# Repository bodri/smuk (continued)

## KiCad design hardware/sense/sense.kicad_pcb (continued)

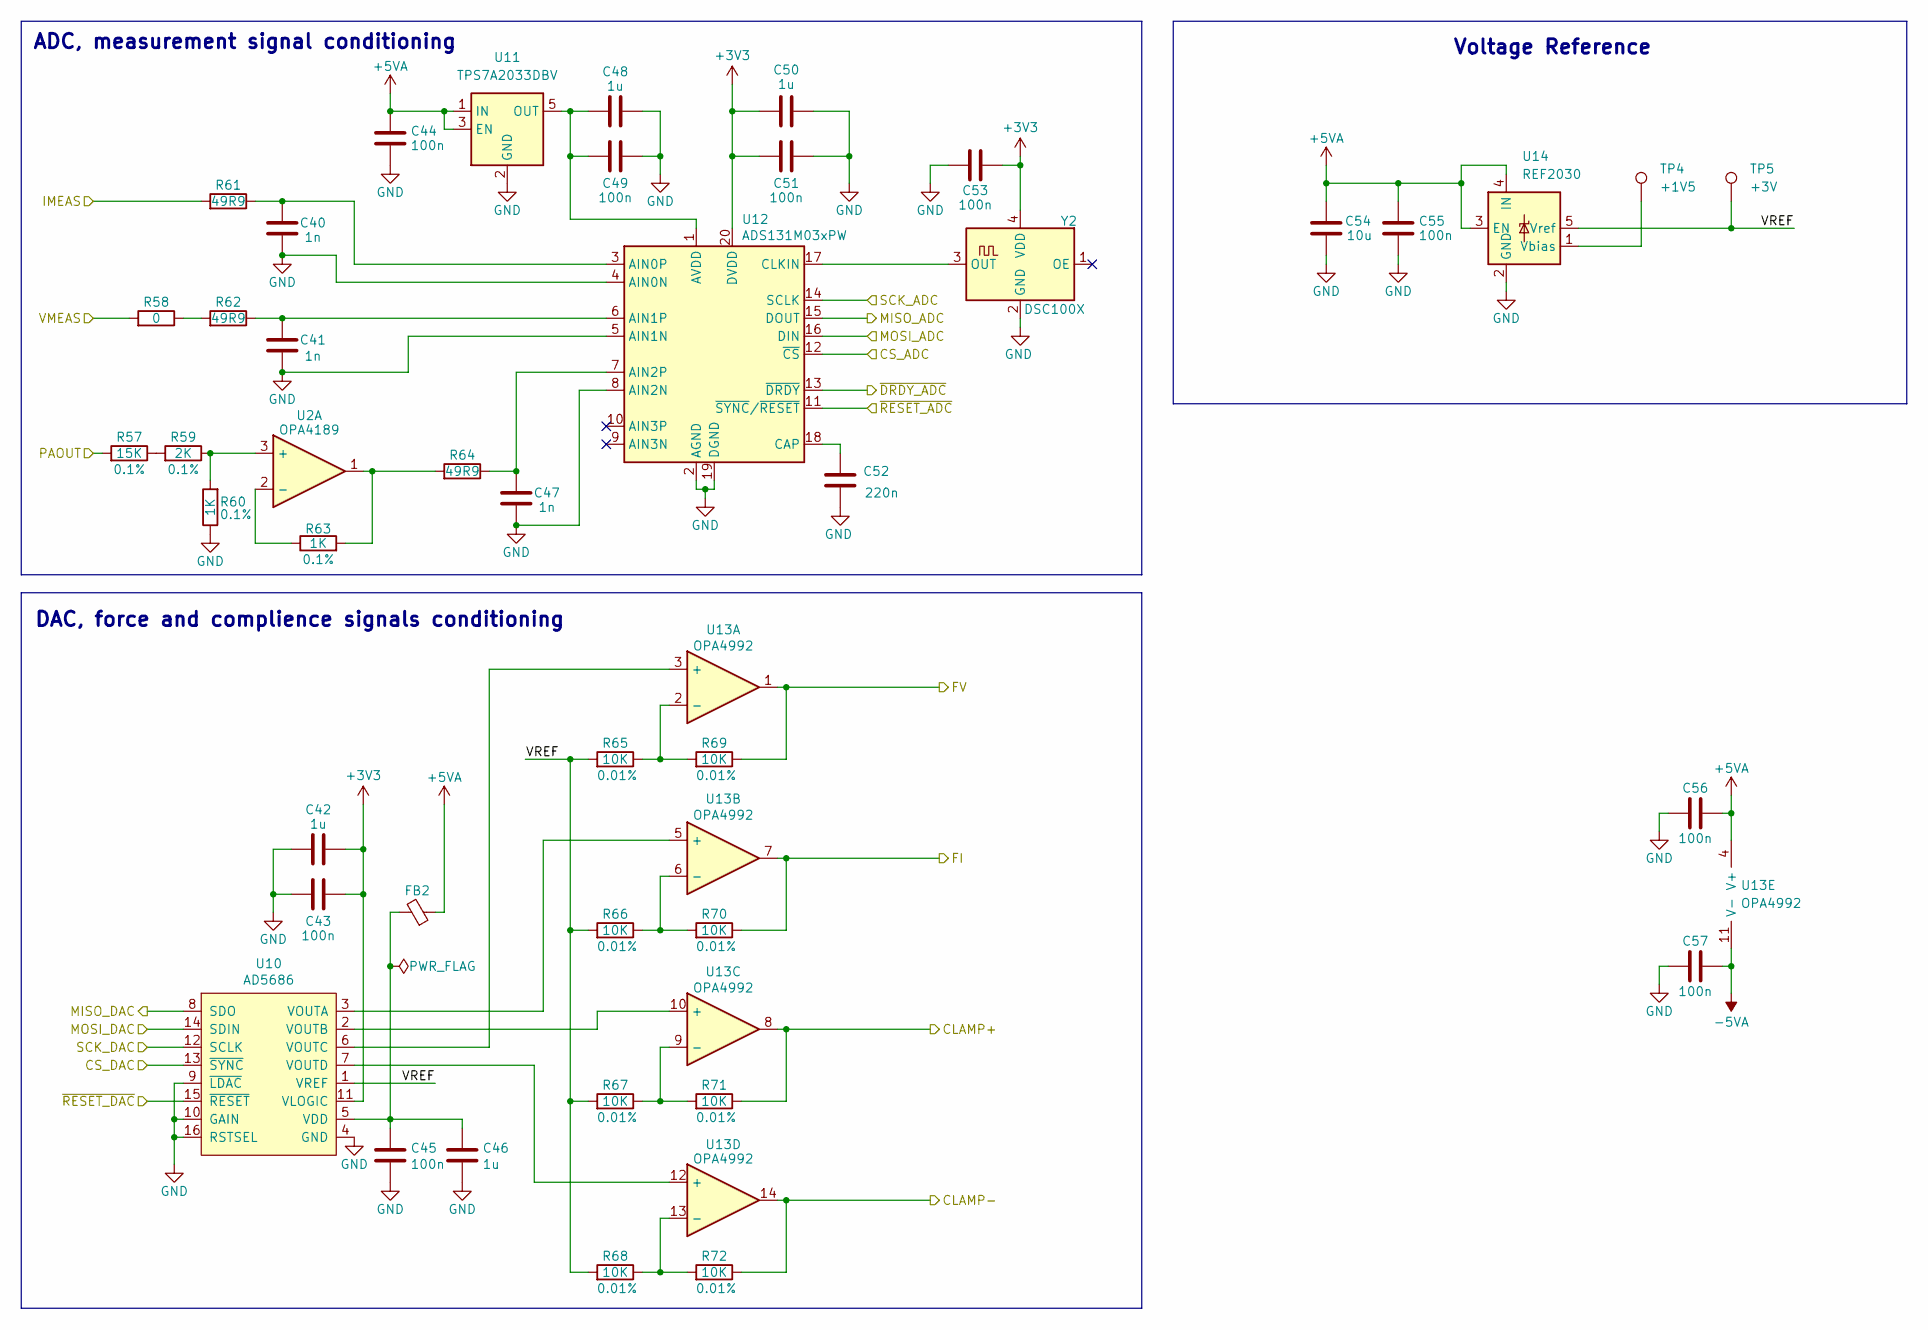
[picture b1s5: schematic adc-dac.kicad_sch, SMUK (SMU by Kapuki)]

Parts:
C40, C41, C47: 1n; C_0603_1608Metric
C42, C46, C48, C50: 1u; C_0603_1608Metric
C43, C44, C45, C49, C51, C53, C55, C56, C57: 100n; C_0603_1608Metric
C52: 220n; C_0603_1608Metric
C54: 10u; C_0603_1608Metric
FB2: FerriteBead_Small; L_0603_1608Metric
R57: 15K; R_0603_1608Metric
R58: 0; R_1206_3216Metric
R59: 2K; R_0603_1608Metric
R60, R63: 1K; R_0603_1608Metric
R61, R62, R64: 49R9; R_0603_1608Metric
R65, R66, R67, R68, R69, R70, R71, R72: 10K; R_0603_1608Metric
TP4: +1V5; TestPoint_Pad_D1.5mm
TP5: +3V; TestPoint_Pad_D1.5mm
U2: OPA4189; TSSOP-14_4.4x5mm_P0.65mm
U10: AD5686; TSSOP-16_4.4x5mm_P0.65mm
U11: TPS7A2033DBV; SOT-23-5
U12: ADS131M03xPW; TSSOP-20_4.4x6.5mm_P0.65mm
U13: OPA4992; TSSOP-14_4.4x5mm_P0.65mm
U14: REF2030; SOT-23-5
Y2: DSC100X; CDFN-4_2.5x3.2mm_P2.1mm

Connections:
+3V3: C42.2, C43.2, C50.2, C51.2, C53.2, U10.11 (VLOGIC), U12.20 (DVDD), Y2.4 (VDD); also elsewhere on the board
+5VA: C44.1, C54.1, C55.1, C56.1, FB2.1, U11.1 (IN), U11.3 (EN), U13.4 (V+), U14.3 (EN), U14.4 (IN); also elsewhere on the board
-5VA: C57.1, U13.11 (V-); also elsewhere on the board
/ADC & DAC/CLAMP+: R71.1, U13.8; also elsewhere on the board
/ADC & DAC/CLAMP-: R72.1, U13.14; also elsewhere on the board
/ADC & DAC/CS_ADC: U12.12 (~CS); also elsewhere on the board
/ADC & DAC/CS_DAC: U10.13 (~SYNC); also elsewhere on the board
/ADC & DAC/FI: R70.1, U13.7; also elsewhere on the board
/ADC & DAC/FV: R69.1, U13.1; also elsewhere on the board
/ADC & DAC/IMEAS: R61.2; also elsewhere on the board
/ADC & DAC/MISO_ADC: U12.15 (DOUT); also elsewhere on the board
/ADC & DAC/MISO_DAC: U10.8 (SDO); also elsewhere on the board
/ADC & DAC/MOSI_ADC: U12.16 (DIN); also elsewhere on the board
/ADC & DAC/MOSI_DAC: U10.14 (SDIN); also elsewhere on the board
/ADC & DAC/PAOUT: R57.2; also elsewhere on the board
/ADC & DAC/SCK_ADC: U12.14 (SCLK); also elsewhere on the board
/ADC & DAC/SCK_DAC: U10.12 (SCLK); also elsewhere on the board
/ADC & DAC/VMEAS: R58.2; also elsewhere on the board
/ADC & DAC/VREF: R65.2, R66.2, R67.2, R68.2, TP5.1 (1_1), U10.1 (VREF), U14.5 (Vref)
/ADC & DAC/~DRDY_ADC: U12.13 (~DRDY); also elsewhere on the board
/ADC & DAC/~RESET_ADC: U12.11 (~SYNC/~RESET); also elsewhere on the board
/ADC & DAC/~RESET_DAC: U10.15 (~RESET); also elsewhere on the board
GND: C40.2, C41.2, C42.1, C43.1, C44.2, C45.2, C46.2, C47.2, C48.1, C49.1, C50.1, C51.1, C52.2, C53.1, C54.2, C55.2, C56.2, C57.2, R60.1, U10.4 (GND), U10.9 (~LDAC), U10.10 (GAIN), U10.16 (RSTSEL), U11.2 (GND), U12.2 (AGND), U12.4 (AIN0N), U12.5 (AIN1N), U12.8 (AIN2N), U12.19 (DGND), U14.2 (GND), Y2.2 (GND); also elsewhere on the board
unnamed: R57.1, R59.2
unnamed: R58.1, R62.2
unnamed: R63.2, R64.2, U2.1
unnamed: R59.1, R60.2, U2.3 (+)
unnamed: R63.1, U2.2 (-)
unnamed: C45.1, C46.1, FB2.2, U10.5 (VDD)
unnamed: U10.3 (VOUTA), U13.5 (+)
unnamed: U10.2 (VOUTB), U13.10 (+)
unnamed: U10.6 (VOUTC), U13.3 (+)
unnamed: U10.7 (VOUTD), U13.12 (+)
unnamed: C48.2, C49.2, U11.5 (OUT), U12.1 (AVDD)
unnamed: C40.1, R61.1, U12.3 (AIN0P)
unnamed: C41.1, R62.1, U12.6 (AIN1P)
unnamed: C47.1, R64.1, U12.7 (AIN2P)
unnamed: C52.1, U12.18 (CAP)
unnamed: U12.17 (CLKIN), Y2.3 (OUT)
unnamed: R65.1, R69.2, U13.2 (-)
unnamed: R66.1, R70.2, U13.6 (-)
unnamed: R67.1, R71.2, U13.9 (-)
unnamed: R68.1, R72.2, U13.13 (-)
unnamed: TP4.1 (1_1), U14.1 (Vbias)

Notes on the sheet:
ADC, measurement signal conditioning
DAC, force and complience signals conditioning
Voltage Reference

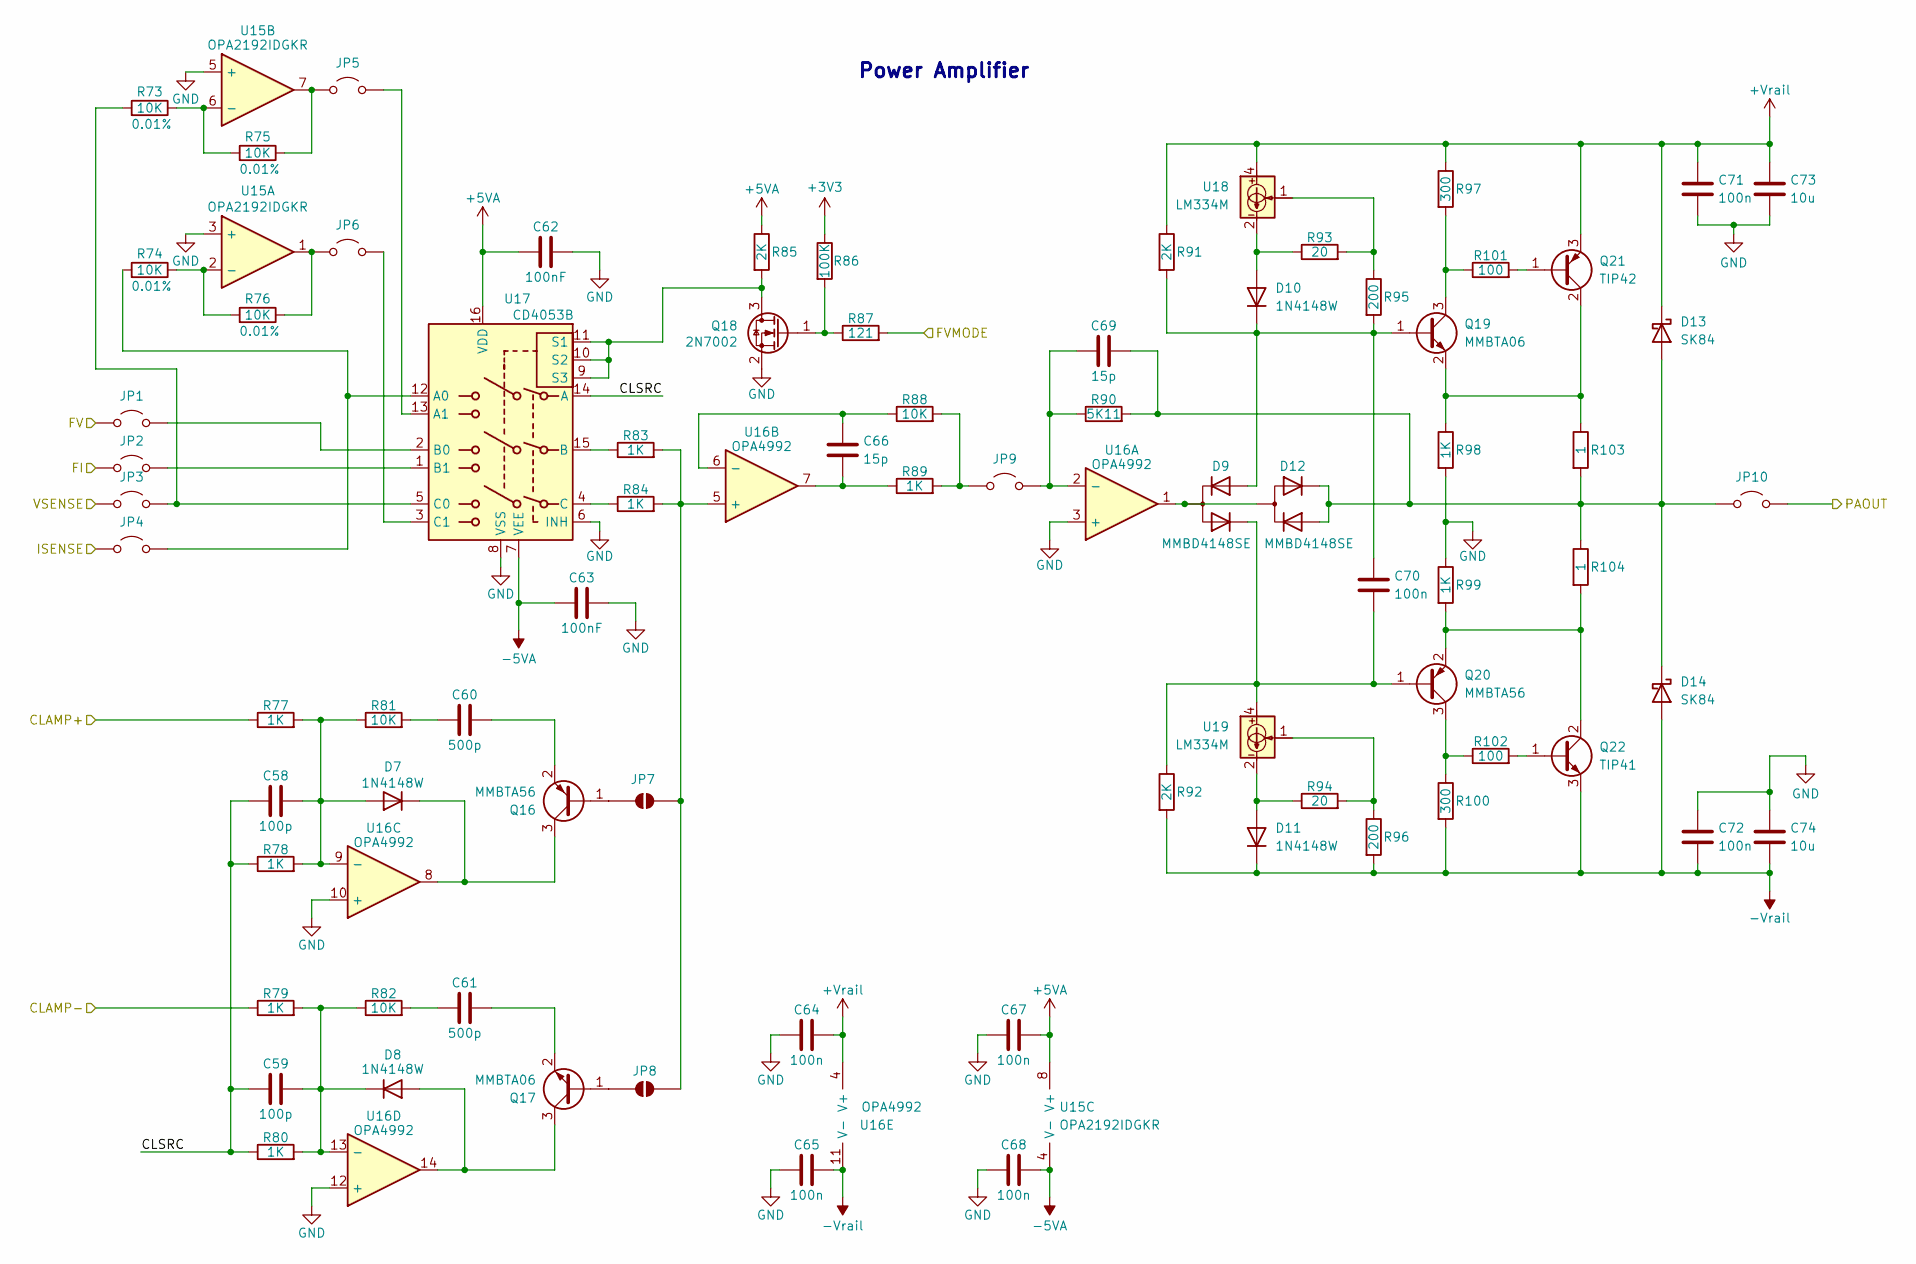
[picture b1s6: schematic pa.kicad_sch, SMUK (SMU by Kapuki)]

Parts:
C58, C59: 100p; C_0603_1608Metric
C60, C61: 500p; C_0603_1608Metric
C62, C63: 100nF; C_0603_1608Metric
C64, C65, C67, C68: 100n; C_0603_1608Metric
C66: 15p; C_0603_1608Metric
C69: 15p; C_1206_3216Metric
C70, C71, C72: 100n; C_1206_3216Metric
C73, C74: 10u; C_1210_3225Metric
D7, D8, D10, D11: 1N4148W; D_SOD-123
D9, D12: MMBD4148SE; SOT-23
D13, D14: SK84; D_SMC
JP1, JP2, JP3, JP4, JP5, JP6, JP9, JP10: Jumper_2_Open; TestPoint_2Pads_Pitch2.54mm_Drill0.8mm
JP7, JP8: SolderJumper_2_Open; SolderJumper-2_P1.3mm_Open_RoundedPad1.0x1.5mm
Q16, Q20: MMBTA56; SOT-23
Q17, Q19: MMBTA06; SOT-23
Q18: 2N7002; SOT-23
Q21: TIP42; TO-220-3_Vertical
Q22: TIP41; TO-220-3_Vertical
R73, R74, R75, R76, R81, R82, R88: 10K; R_0603_1608Metric
R77, R78, R79, R80, R89: 1K; R_0603_1608Metric
R83, R84: 1K; R_1206_3216Metric
R85: 2K; R_0603_1608Metric
R86: 100K; R_0603_1608Metric
R87: 121; R_0603_1608Metric
R90: 5K11; R_1206_3216Metric
R91, R92: 2K; R_1206_3216Metric
R93, R94: 20; R_0805_2012Metric
R95, R96: 200; R_0805_2012Metric
R97, R100: 300; R_0805_2012Metric
R98, R99: 1K; R_2512_6332Metric
R101, R102: 100; R_0805_2012Metric
R103, R104: 1; R_2512_6332Metric
U15: OPA2192IDGKR; VSSOP-8_3x3mm_P0.65mm
U16: OPA4992; TSSOP-14_4.4x5mm_P0.65mm
U17: CD4053B; TSSOP-16_4.4x5mm_P0.65mm
U18, U19: LM334M; SOIC-8_3.9x4.9mm_P1.27mm

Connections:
+3V3: R86.1; also elsewhere on the board
+5VA: C62.1, C67.1, R85.1, U15.8 (V+), U17.16 (VDD); also elsewhere on the board
+Vrail: C64.1, C71.1, C73.1, D13.1 (K), Q21.3 (E), R91.1, R97.1, U16.4 (V+), U18.4; also elsewhere on the board
-5VA: C63.1, C68.1, U15.4 (V-), U17.7 (VEE); also elsewhere on the board
-Vrail: C65.1, C72.2, C74.2, D11.1 (K), D14.2 (A), Q22.3 (E), R92.2, R96.2, R100.2, U16.11 (V-); also elsewhere on the board
/ADC & DAC/CLAMP+: R77.1; also elsewhere on the board
/ADC & DAC/CLAMP-: R79.1; also elsewhere on the board
/ADC & DAC/FI: JP2.1 (A); also elsewhere on the board
/ADC & DAC/FV: JP1.1 (A); also elsewhere on the board
/ADC & DAC/PAOUT: JP10.2 (B); also elsewhere on the board
/Current Sense/ISENSE: JP4.1 (A); also elsewhere on the board
/Floating MCU/FVMODE: R87.2; also elsewhere on the board
/Power Amplifier/CLSRC: C58.1, C59.1, R78.1, R80.1, U17.14 (A)
/Power Amplifier/VSENSE: JP3.1 (A); also elsewhere on the board
GND: C62.2, C63.2, C64.2, C65.2, C67.2, C68.2, C71.2, C72.1, C73.2, C74.1, Q18.2 (S), R98.2, R99.1, U15.3 (+), U15.5 (+), U16.3 (+), U16.10 (+), U16.12 (+), U17.6 (INH), U17.8 (VSS); also elsewhere on the board
unnamed: C60.1, R81.2
unnamed: C61.1, R82.2
unnamed: C66.2, R89.1, U16.7
unnamed: C58.2, D7.2 (A), R77.2, R78.2, R81.1, U16.9 (-)
unnamed: D7.1 (K), Q16.3 (C), U16.8
unnamed: D8.2 (A), Q17.3 (C), U16.14
unnamed: C59.2, D8.1 (K), R79.2, R80.2, R82.1, U16.13 (-)
unnamed: D10.2 (A), R93.1, U18.2, U18.3, U18.6, U18.7
unnamed: C70.1, D9.1, D10.1 (K), Q19.1 (B), R91.2, R95.2
unnamed: D11.2 (A), R94.1, U19.2, U19.3, U19.6, U19.7
unnamed: D9.3, D12.3, U16.1
unnamed: C69.2, D12.1, D12.2, D13.2 (A), D14.1 (K), JP10.1 (A), R90.2, R103.2, R104.1
unnamed: JP1.2 (B), U17.2 (B0)
unnamed: JP2.2 (B), U17.1 (B1)
unnamed: JP3.2 (B), R73.2, U17.5 (C0)
unnamed: JP4.2 (B), R74.2, U17.12 (A0)
unnamed: JP5.1 (A), R75.1, U15.7
unnamed: JP5.2 (B), U17.13 (A1)
unnamed: JP6.1 (A), R76.1, U15.1
unnamed: JP6.2 (B), U17.3 (C1)
unnamed: JP7.1 (A), Q16.1 (B)
unnamed: JP7.2 (B), JP8.2 (B), R83.2, R84.2, U16.5 (+)
unnamed: JP8.1 (A), Q17.1 (B)
unnamed: JP9.1 (A), R88.2, R89.2
unnamed: C69.1, JP9.2 (B), R90.1, U16.2 (-)
unnamed: C60.2, Q16.2 (E)
unnamed: C61.2, Q17.2 (E)
unnamed: Q18.3 (D), R85.2, U17.9 (S3), U17.10 (S2), U17.11 (S1)
unnamed: Q18.1 (G), R86.2, R87.1
unnamed: Q19.3 (C), R97.2, R101.1
unnamed: Q19.2 (E), Q21.2 (C), R98.1, R103.1
unnamed: C70.2, D9.2, Q20.1 (B), R92.1, U19.4
unnamed: Q20.3 (C), R100.1, R102.1
unnamed: Q20.2 (E), Q22.2 (C), R99.2, R104.2
unnamed: Q21.1 (B), R101.2
unnamed: Q22.1 (B), R102.2
unnamed: R93.2, R95.1, U18.1
unnamed: R94.2, R96.1, U19.1
unnamed: R74.1, R76.2, U15.2 (-)
unnamed: R73.1, R75.2, U15.6 (-)
unnamed: C66.1, R88.1, U16.6 (-)
unnamed: R83.1, U17.15 (B)
unnamed: R84.1, U17.4 (C)

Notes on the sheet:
Power Amplifier

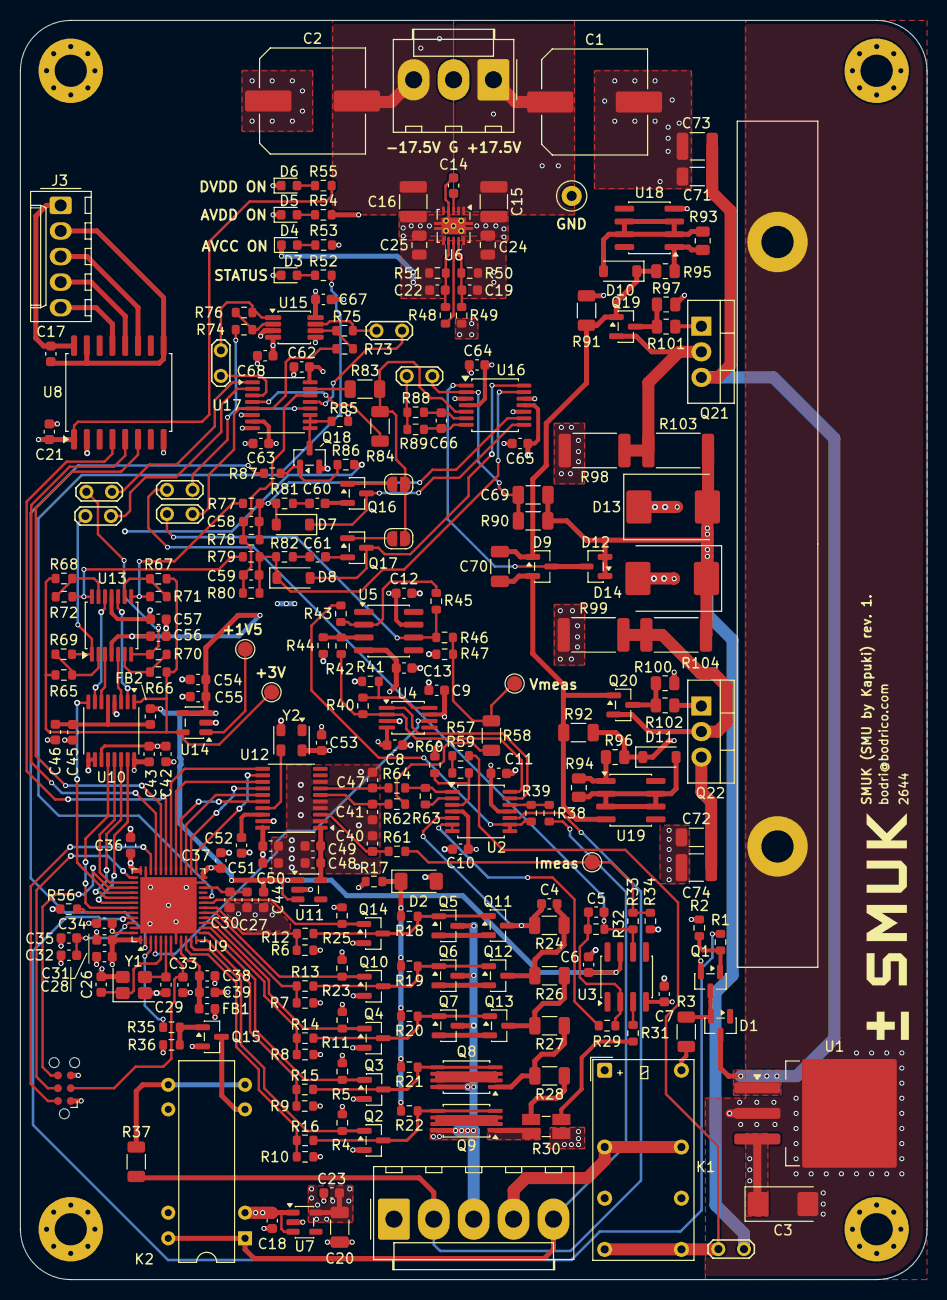
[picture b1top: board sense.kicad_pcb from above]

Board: 4 copper layers, 90.0 x 125.0 mm, 263 parts (0 on the bottom side), 172 nets.

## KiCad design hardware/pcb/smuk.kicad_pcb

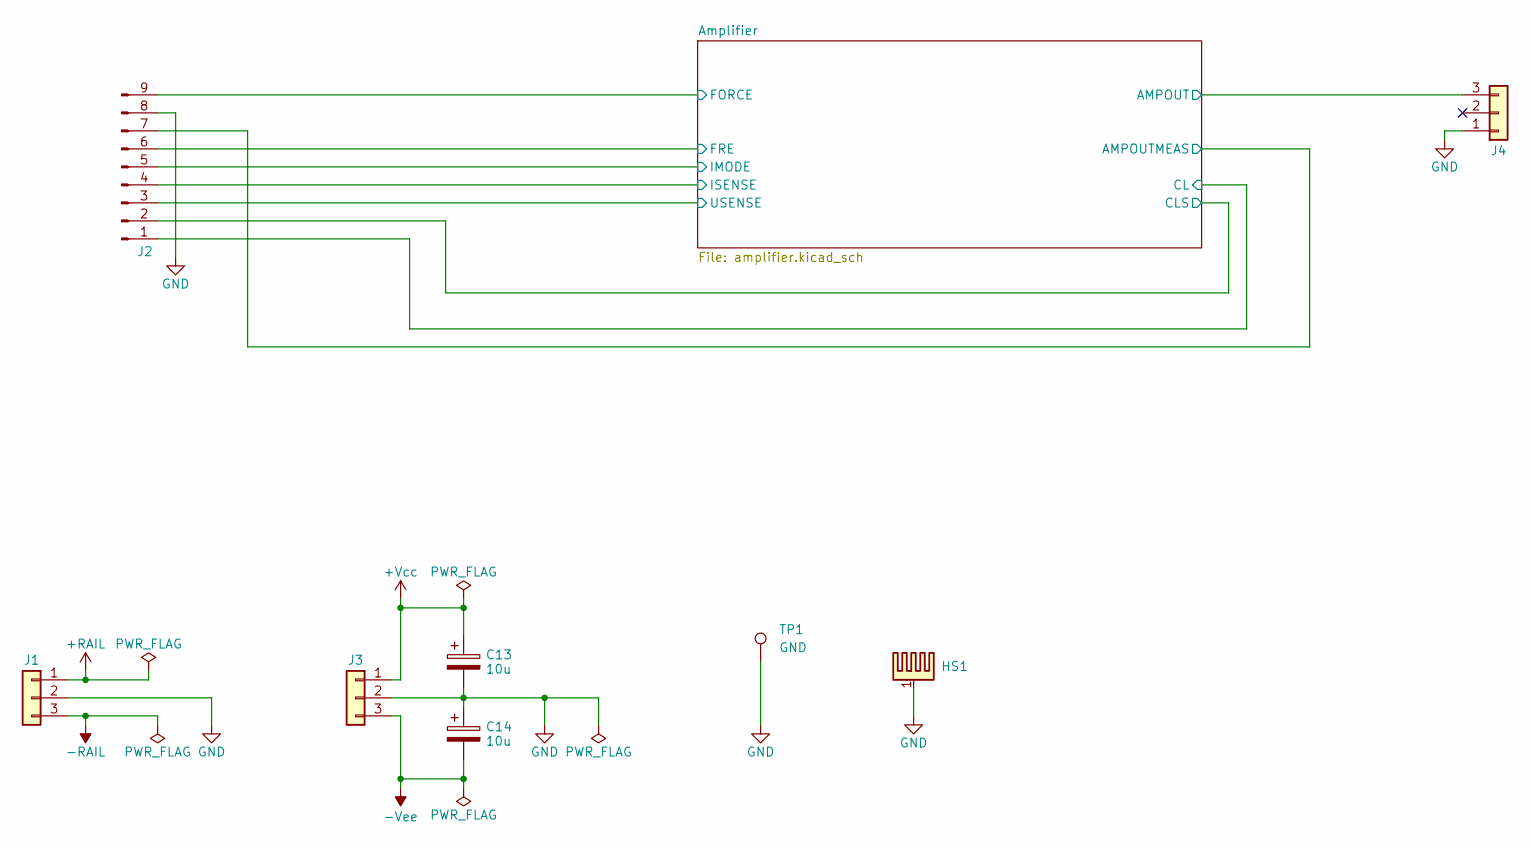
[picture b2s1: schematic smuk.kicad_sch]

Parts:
C13, C14: 10u; CP_EIA-6032-28_Kemet-C
HS1: Heatsink_Pad; Heatsink_Fischer_SK96-84SA_2Fixations
J1, J3, J4: Conn_01x03; Molex_KK-396_A-41791-0003_1x03_P3.96mm_Vertical
J2: Conn_01x09_Pin; PinHeader_1x09_P2.54mm_Horizontal
TP1: GND; TestPoint_Loop_D1.80mm_Drill1.0mm_Beaded

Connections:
+RAIL: J1.1; also elsewhere on the board
+Vcc: C13.1, J3.1; also elsewhere on the board
-RAIL: J1.3; also elsewhere on the board
-Vee: C14.2, J3.3; also elsewhere on the board
/Amplifier/AMPOUT: J4.3; also elsewhere on the board
/Amplifier/AMPOUTMEAS: J2.7; also elsewhere on the board
/Amplifier/CL: J2.1; also elsewhere on the board
/Amplifier/CLS: J2.2; also elsewhere on the board
/Amplifier/FORCE: J2.9; also elsewhere on the board
/Amplifier/FRE: J2.6; also elsewhere on the board
/Amplifier/IMODE: J2.5; also elsewhere on the board
/Amplifier/ISENSE: J2.4; also elsewhere on the board
/Amplifier/USENSE: J2.3; also elsewhere on the board
GND: C13.2, C14.1, HS1.1, J1.2, J2.8, J3.2, J4.1, TP1.1 (1_1); also elsewhere on the board

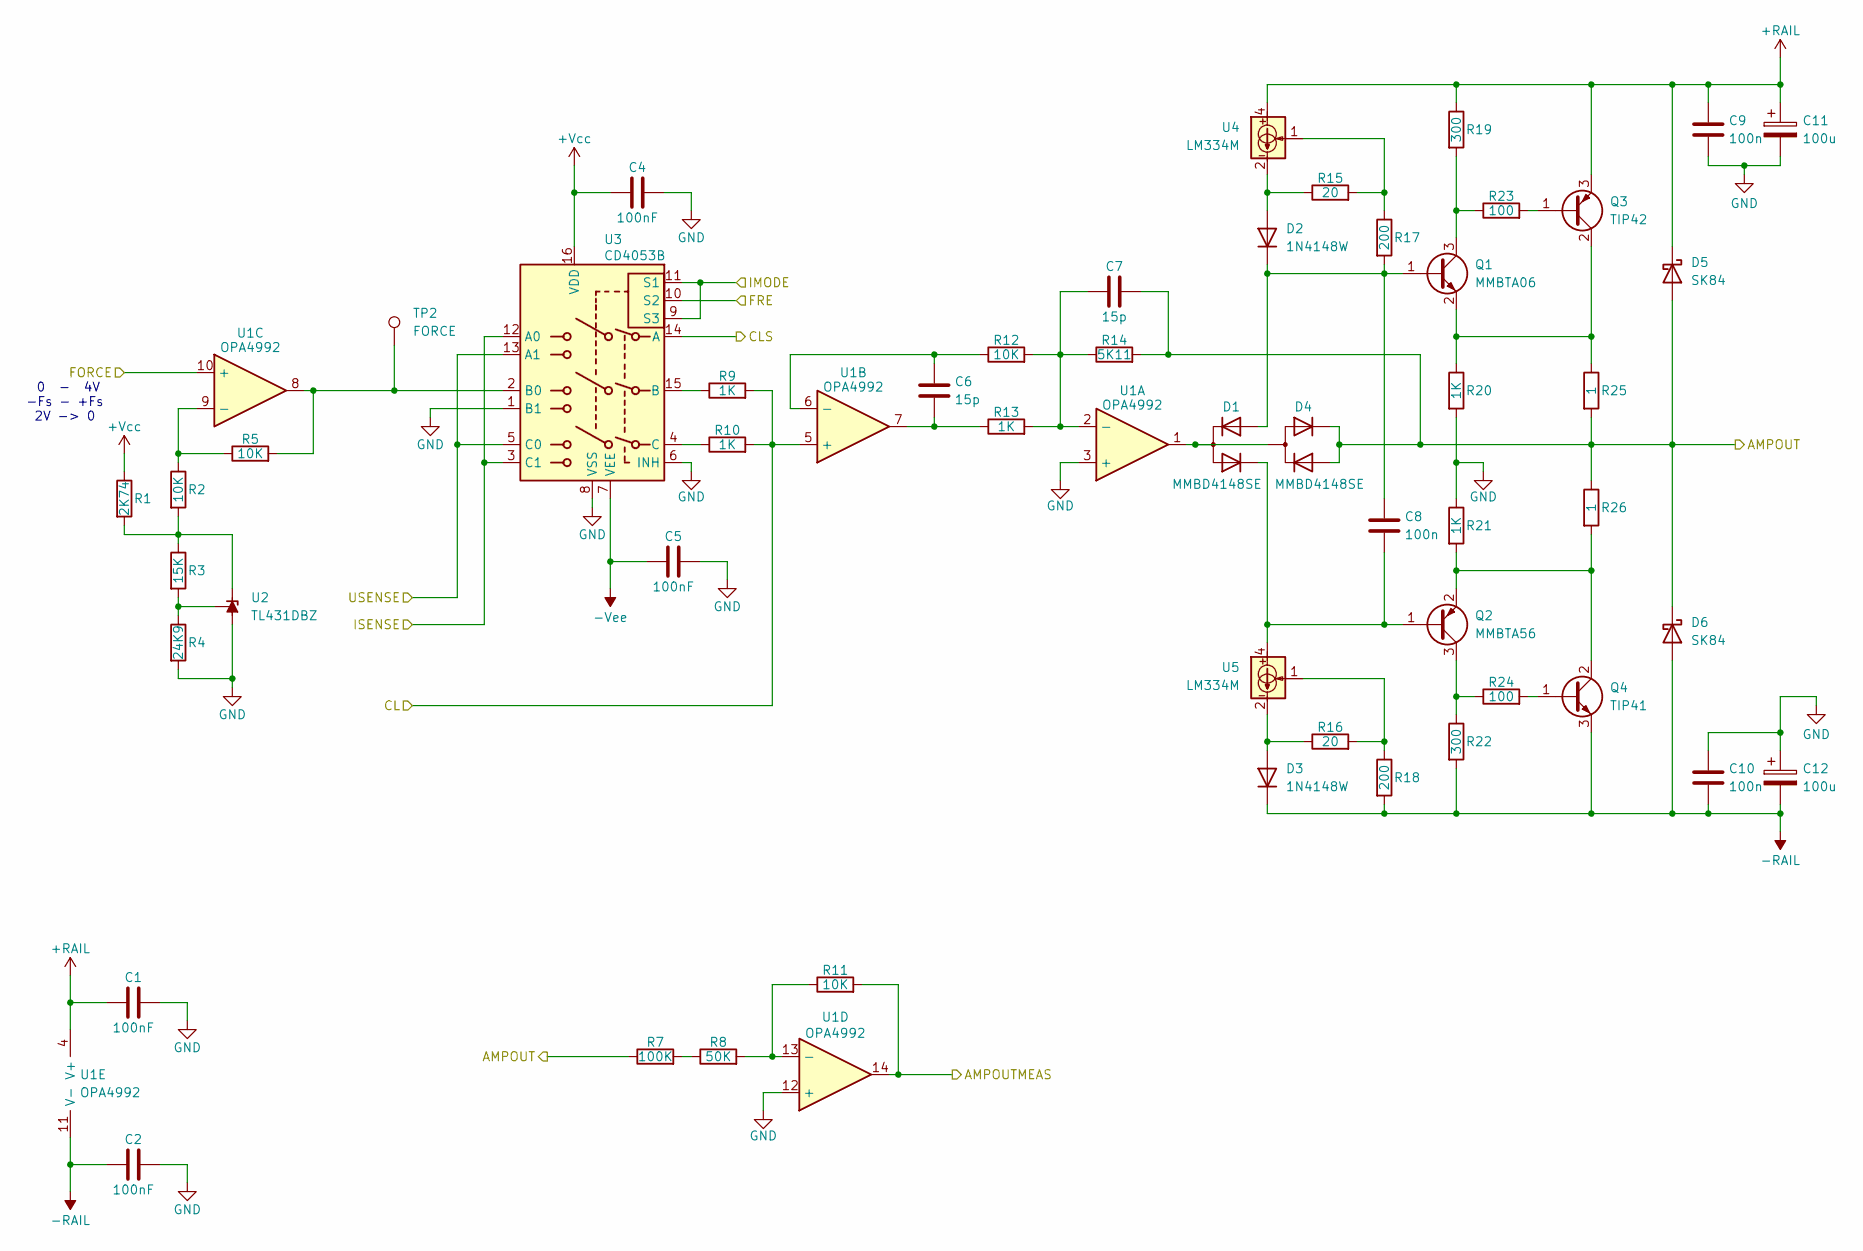
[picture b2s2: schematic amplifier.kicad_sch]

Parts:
C1, C2, C4, C5: 100nF; C_0805_2012Metric
C6: 15p; C_1206_3216Metric
C7: 15p; C_0805_2012Metric
C8: 100n; C_1206_3216Metric
C9, C10: 100n; C_0805_2012Metric
C11, C12: 100u; C_Elec_10x10.2
D1, D4: MMBD4148SE; SOT-23
D2, D3: 1N4148W; D_SOD-123
D5, D6: SK84; D_SMC
Q1: MMBTA06; SOT-23
Q2: MMBTA56; SOT-23
Q3: TIP42; TO-220-3_Vertical
Q4: TIP41; TO-220-3_Vertical
R1: 2K74; R_0805_2012Metric
R2, R5, R11, R12: 10K; R_0805_2012Metric
R3: 15K; R_0805_2012Metric
R4: 24K9; R_0805_2012Metric
R7: 100K; R_0805_2012Metric
R8: 50K; R_0805_2012Metric
R9, R10: 1K; R_1206_3216Metric
R13: 1K; R_0805_2012Metric
R14: 5K11; R_0805_2012Metric
R15, R16: 20; R_0805_2012Metric
R17, R18: 200; R_0805_2012Metric
R19, R22: 300; R_0805_2012Metric
R20, R21: 1K; R_2512_6332Metric
R23, R24: 100; R_0805_2012Metric
R25, R26: 1; R_2512_6332Metric
TP2: FORCE; TestPoint_Loop_D1.80mm_Drill1.0mm_Beaded
U1: OPA4992; TSSOP-14_4.4x5mm_P0.65mm
U2: TL431DBZ; SOT-23
U3: CD4053B; TSSOP-16_4.4x5mm_P0.65mm
U4, U5: LM334M; SOIC-8_3.9x4.9mm_P1.27mm

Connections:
+RAIL: C1.1, C9.1, C11.1, D5.1 (K), Q3.3 (E), R19.1, U1.4 (V+), U4.4; also elsewhere on the board
+Vcc: C4.1, R1.1, U3.16 (VDD); also elsewhere on the board
-RAIL: C2.1, C10.2, C12.2, D3.1 (K), D6.2 (A), Q4.3 (E), R18.2, R22.2, U1.11 (V-); also elsewhere on the board
-Vee: C5.1, U3.7 (VEE); also elsewhere on the board
/Amplifier/AMPOUT: C7.2, D4.1, D4.2, D5.2 (A), D6.1 (K), R7.1, R14.2, R25.2, R26.1; also elsewhere on the board
/Amplifier/AMPOUTMEAS: R11.2, U1.14; also elsewhere on the board
/Amplifier/CL: R9.2, R10.2, U1.5 (+); also elsewhere on the board
/Amplifier/CLS: U3.14 (A); also elsewhere on the board
/Amplifier/FORCE: U1.10 (+); also elsewhere on the board
/Amplifier/FRE: U3.10 (S2); also elsewhere on the board
/Amplifier/IMODE: U3.9 (S3), U3.11 (S1); also elsewhere on the board
/Amplifier/ISENSE: U3.3 (C1), U3.12 (A0); also elsewhere on the board
/Amplifier/USENSE: U3.5 (C0), U3.13 (A1); also elsewhere on the board
GND: C1.2, C2.2, C4.2, C5.2, C9.2, C10.1, C11.2, C12.1, R4.2, R20.2, R21.1, U1.3 (+), U1.12 (+), U2.3 (A), U3.1 (B1), U3.6 (INH), U3.8 (VSS); also elsewhere on the board
unnamed: C6.2, R13.1, U1.7
unnamed: D1.3, D4.3, U1.1
unnamed: D2.2 (A), R15.1, U4.2, U4.3, U4.6, U4.7
unnamed: C8.1, D1.1, D2.1 (K), Q1.1 (B), R17.2
unnamed: D3.2 (A), R16.1, U5.2, U5.3, U5.6, U5.7
unnamed: Q1.3 (C), R19.2, R23.1
unnamed: Q1.2 (E), Q3.2 (C), R20.1, R25.1
unnamed: C8.2, D1.2, Q2.1 (B), U5.4
unnamed: Q2.3 (C), R22.1, R24.1
unnamed: Q2.2 (E), Q4.2 (C), R21.2, R26.2
unnamed: Q3.1 (B), R23.2
unnamed: Q4.1 (B), R24.2
unnamed: R7.2, R8.1
unnamed: R15.2, R17.1, U4.1
unnamed: R16.2, R18.1, U5.1
unnamed: C7.1, R12.2, R13.2, R14.1, U1.2 (-)
unnamed: C6.1, R12.1, U1.6 (-)
unnamed: R2.1, R5.1, U1.9 (-)
unnamed: R8.2, R11.1, U1.13 (-)
unnamed: R1.2, R2.2, R3.1, U2.1 (K)
unnamed: R3.2, R4.1, U2.2 (REF)
unnamed: R5.2, TP2.1 (1_1), U1.8, U3.2 (B0)
unnamed: R9.1, U3.15 (B)
unnamed: R10.1, U3.4 (C)

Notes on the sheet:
0 - 4V -Fs - +Fs 2V -> 0

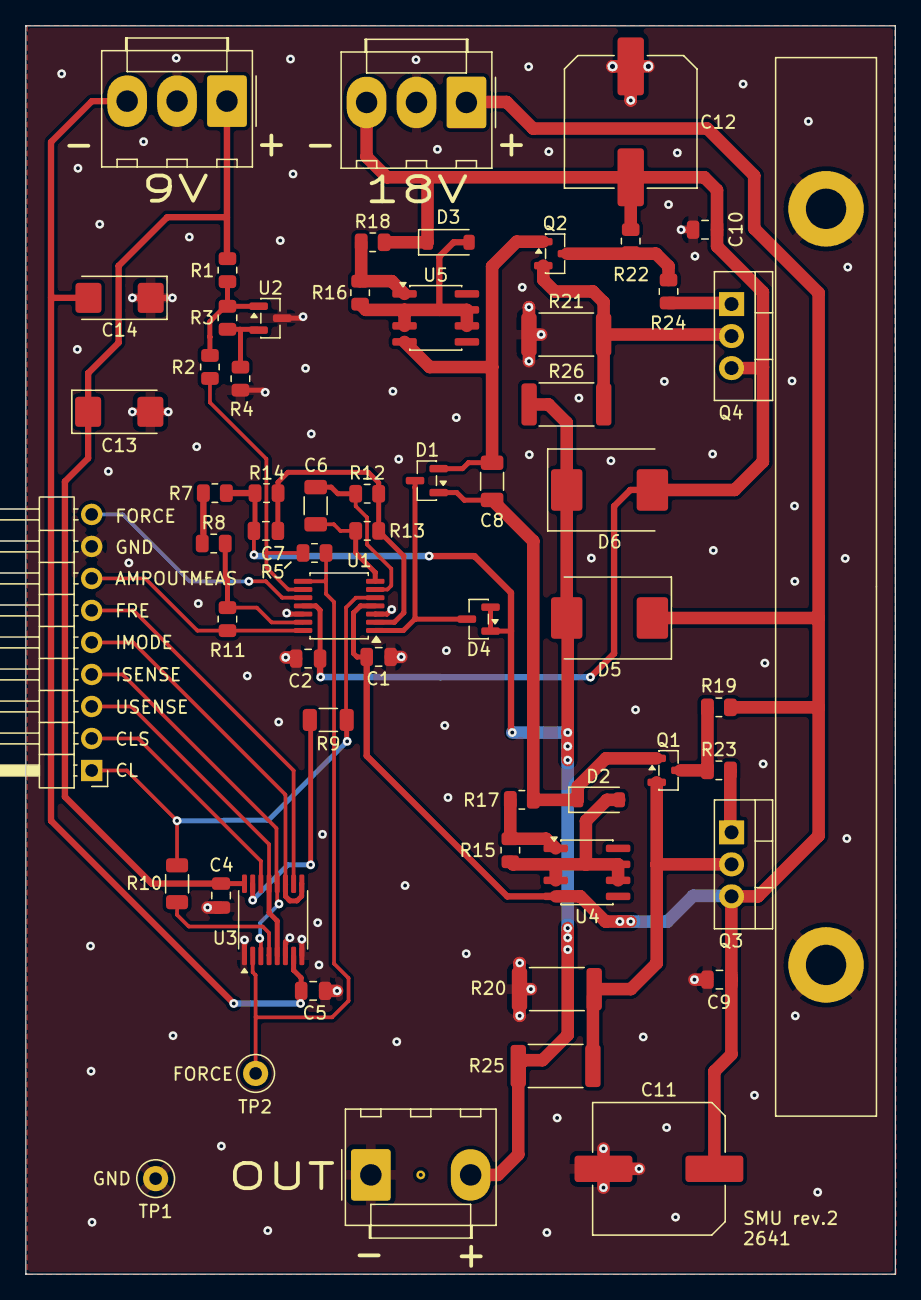
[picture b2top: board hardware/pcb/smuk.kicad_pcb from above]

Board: 2 copper layers, 69.0 x 99.1 mm, 60 parts (0 on the bottom side), 38 nets.

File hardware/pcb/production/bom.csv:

Designator,Footprint,Quantity,Value,LCSC Part #
"C1, C2, C4, C5",0805,4,100nF,
"C10, C9",0805,2,100n,
"C11, C12",C_Elec_10x10.2,2,100u,
"C13, C14",CP_EIA-6032-28_Kemet-C,2,10u,
C6,1206,1,15p,
C7,0805,1,15p,
C8,1206,1,100n,
"D1, D4",SOT-23,2,MMBD4148SE,
"D2, D3",D_SOD-123,2,1N4148W,
"D5, D6",D_SMC,2,SK84,
HS1,Heatsink_Fischer_SK96-84SA_2Fixations,1,Heatsink_Pad,
"J1, J3, J4",Molex_KK-396_A-41791-0003_1x03_P3.96mm_Vertical,3,Conn_01x03,
J2,PinHeader_1x09_P2.54mm_Horizontal,1,Conn_01x09_Pin,
Q1,SOT-23,1,MMBTA06,
Q2,SOT-23,1,MMBTA56,
Q3,TO-220-3_Vertical,1,TIP42,
Q4,TO-220-3_Vertical,1,TIP41,
R1,0805,1,2K74,
"R10, R9",1206,2,1K,
"R11, R12, R2, R5",0805,4,10K,
R13,0805,1,1K,
R14,0805,1,5K11,
"R15, R16",0805,2,20,
"R17, R18",0805,2,200,
"R19, R22",0805,2,300,
"R20, R21",2512,2,1K,
"R23, R24",0805,2,100,
"R25, R26",2512,2,1,
R3,0805,1,15K,
R4,0805,1,24K9,
R7,0805,1,100K,
R8,0805,1,50K,
TP1,TestPoint_Loop_D1.80mm_Drill1.0mm_Beaded,1,GND,
TP2,TestPoint_Loop_D1.80mm_Drill1.0mm_Beaded,1,FORCE,
U1,TSSOP-14_4.4x5mm_P0.65mm,1,OPA4992,
U2,SOT-23,1,TL431DBZ,
U3,TSSOP-16_4.4x5mm_P0.65mm,1,CD4053B,
"U4, U5",SOIC-8_3.9x4.9mm_P1.27mm,2,LM334M,

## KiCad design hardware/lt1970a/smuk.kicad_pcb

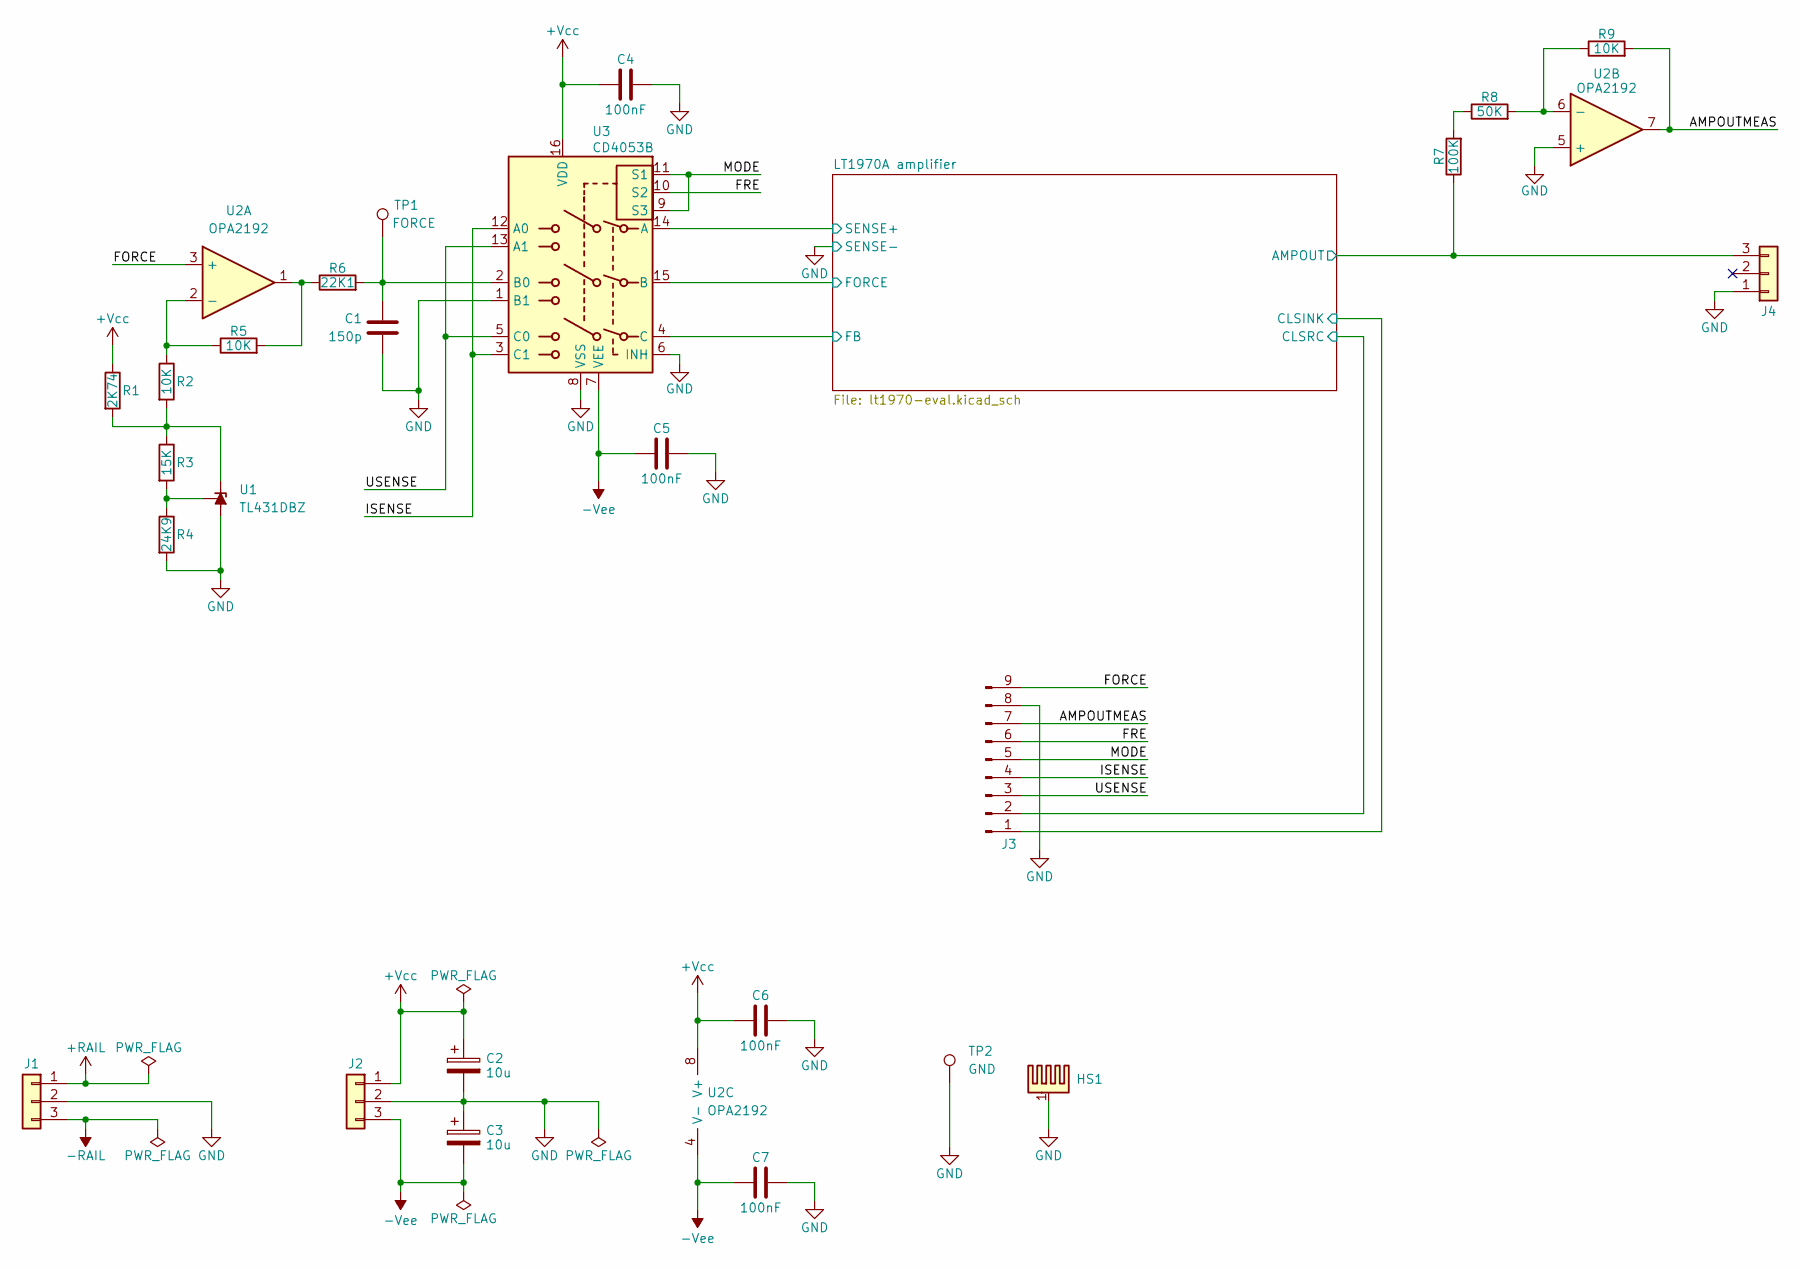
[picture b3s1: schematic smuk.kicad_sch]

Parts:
C1: 150p; C_0603_1608Metric
C2, C3: 10u; CP_EIA-6032-28_Kemet-C
C4, C5, C6, C7: 100nF; C_0603_1608Metric
HS1: Heatsink_Pad; Heatsink_Fischer_SK96-84SA_2Fixations
J1, J2, J4: Conn_01x03; Molex_KK-396_A-41791-0003_1x03_P3.96mm_Vertical
J3: Conn_01x09_Pin; PinHeader_1x09_P2.54mm_Horizontal
R1: 2K74; R_0603_1608Metric
R2, R5, R9: 10K; R_0603_1608Metric
R3: 15K; R_0603_1608Metric
R4: 24K9; R_0603_1608Metric
R6: 22K1; R_0603_1608Metric
R7: 100K; R_0603_1608Metric
R8: 50K; R_0603_1608Metric
TP1: FORCE; TestPoint_Loop_D1.80mm_Drill1.0mm_Beaded
TP2: GND; TestPoint_Loop_D1.80mm_Drill1.0mm_Beaded
U1: TL431DBZ; SOT-23
U2: OPA2192; VSSOP-8_3x3mm_P0.65mm
U3: CD4053B; TSSOP-16_4.4x5mm_P0.65mm

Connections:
/AMPOUTMEAS: J3.7, R9.2, U2.7
/FORCE: J3.9, U2.3 (+)
/FRE: J3.6, U3.10 (S2)
/ISENSE: J3.4, U3.3 (C1), U3.12 (A0)
/LT1970A amplifier/AMPOUT: J4.3, R7.1; also elsewhere on the board
/LT1970A amplifier/CLSINK: J3.1; also elsewhere on the board
/LT1970A amplifier/CLSRC: J3.2; also elsewhere on the board
/LT1970A amplifier/FB: U3.4 (C); also elsewhere on the board
/LT1970A amplifier/FORCE: U3.15 (B); also elsewhere on the board
/LT1970A amplifier/SENSE+: U3.14 (A); also elsewhere on the board
/MODE: J3.5, U3.9 (S3), U3.11 (S1)
/USENSE: J3.3, U3.5 (C0), U3.13 (A1)
GND: C1.2, C2.2, C3.1, C4.2, C5.2, C6.2, C7.2, HS1.1, J1.2, J2.2, J3.8, J4.1, R4.2, TP2.1 (1_1), U1.3 (A), U2.5 (+), U3.1 (B1), U3.6 (INH), U3.8 (VSS); also elsewhere on the board
unnamed: R5.2, R6.1, U2.1
unnamed: R7.2, R8.1
unnamed: R1.2, R2.2, R3.1, U1.1 (K)
unnamed: R3.2, R4.1, U1.2 (REF)
unnamed: R2.1, R5.1, U2.2 (-)
unnamed: R8.2, R9.1, U2.6 (-)
unnamed: C1.1, R6.2, TP1.1 (1_1), U3.2 (B0)
